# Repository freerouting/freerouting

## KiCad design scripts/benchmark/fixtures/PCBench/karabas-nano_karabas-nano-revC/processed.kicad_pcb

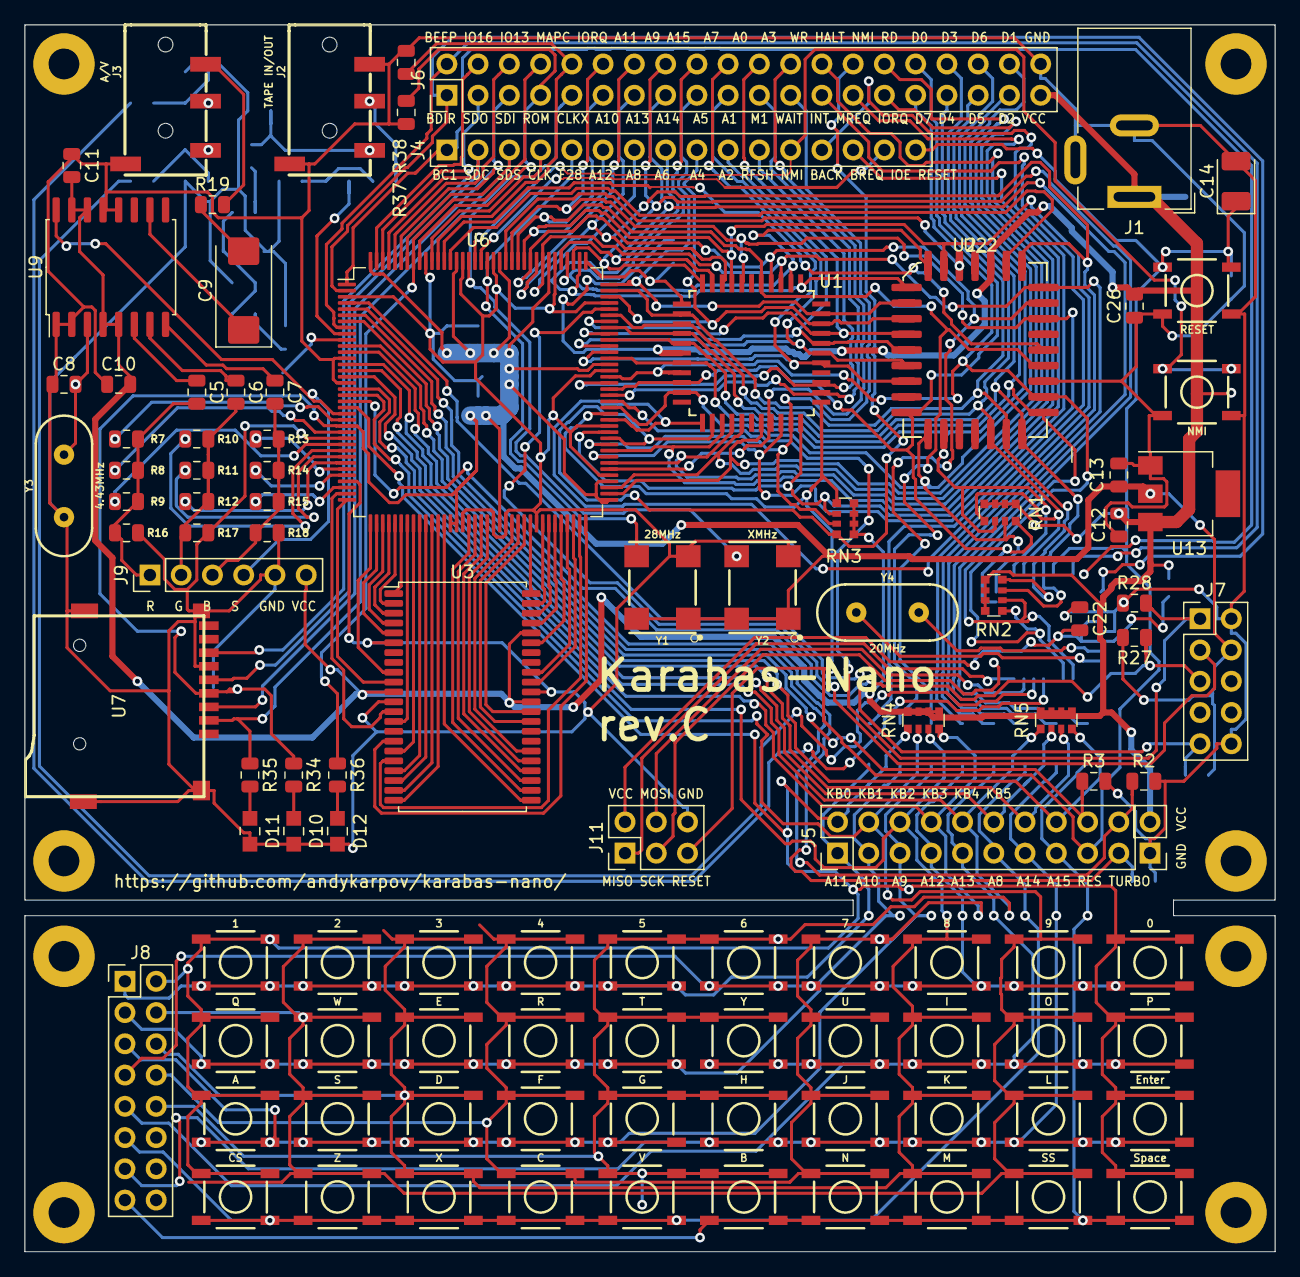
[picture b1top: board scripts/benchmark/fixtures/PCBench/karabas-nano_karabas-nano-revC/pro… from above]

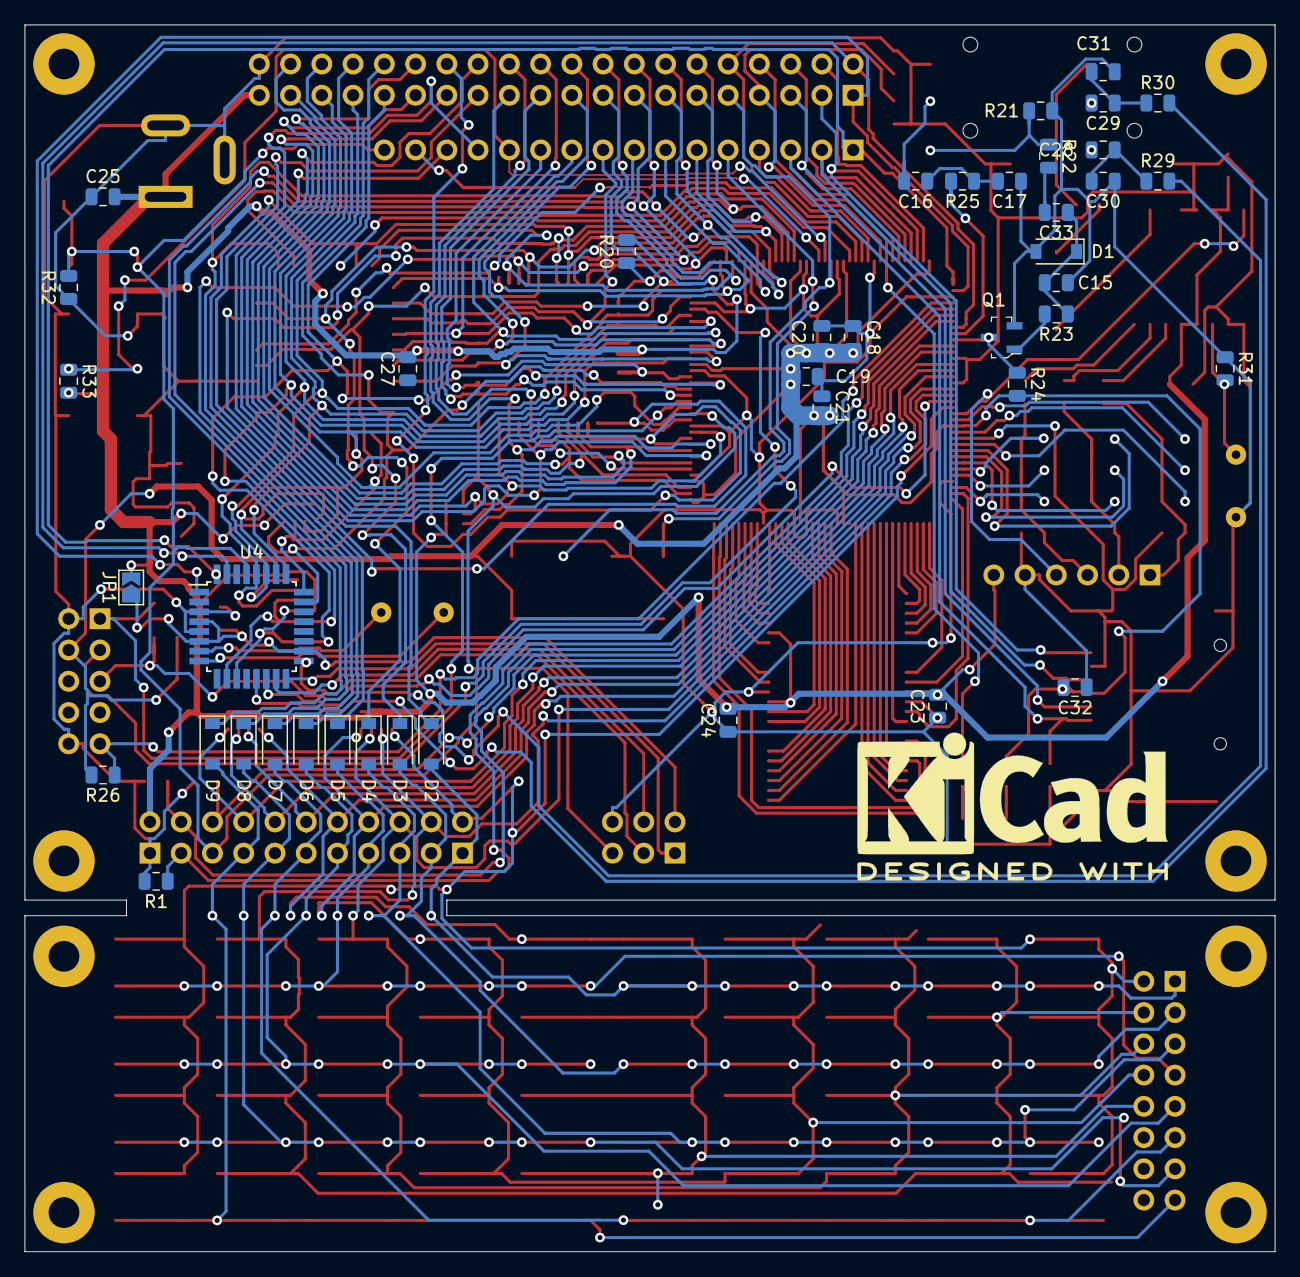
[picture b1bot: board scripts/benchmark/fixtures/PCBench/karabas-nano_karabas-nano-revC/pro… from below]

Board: 2 copper layers, 101.6 x 99.7 mm, 157 parts (42 on the bottom side), 162 nets.

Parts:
C5, C6, C7, C16, C18, C19, C20, C21, C22, C23, C24, C25, C26, C27, C32: 100nF; C_0805_2012Metric
C8: 10p; C_0805_2012Metric
C9: 220uF; CP_EIA-7343-31_Kemet-D_Pad2.25x2.55mm_HandSolder
C10, C11, C12, C13, C28, C29: 10uF; C_0805_2012Metric
C14: 10uF; CP_EIA-3528-21_Kemet-B_Pad1.50x2.35mm_HandSolder
C15, C33: 10nF; C_0805_2012Metric
C17: 3n3; C_0805_2012Metric
C30, C31: 1nF; C_0805_2012Metric
D1, D2, D3, D4, D5, D6, D7, D8, D9: 1N4148W; D_SOD-123
D10: PWR; 0805
D11: SD; 0805
D12: MMC; 0805
H1, H2, H3, H4, H5, H6, H7, H8: MountingHole; MountingHole_2.5mm_Pad
J1: DC 5V; BarrelJack_Wuerth_6941xx301002
J2: TAPE IN/OUT; AUDIO_JACK_3.5MM_SMD
J3: A/V; AUDIO_JACK_3.5MM_SMD
J4: BUS; PinHeader_1x16_P2.54mm_Vertical
J5: KEYBOARD; PinHeader_2x10_P2.54mm_Vertical
J6: BUS; PinHeader_2x20_P2.54mm_Vertical
J7: JTAG; PinHeader_2x05_P2.54mm_Vertical
J8: KEYBOARD; PinHeader_2x08_P2.54mm_Vertical
J9: RGB; PinHeader_1x06_P2.54mm_Vertical
J10: PWR; PinHeader_1x02_P2.54mm_Vertical
J11: AVR ISP; PinHeader_2x03_P2.54mm_Vertical
JP1: SolderJumper_2_Open; SolderJumper-2_P1.3mm_Open_TrianglePad1.0x1.5mm
Q1: BC846B; SOT-23-3
R1, R2, R3, R21, R23, R24, R26, R27, R28, R29, R30, R33, R37, R38: 10k; R_0805_2012Metric
R7, R10, R13, R22: 510; R_0805_2012Metric
R8, R11, R14: 1k; R_0805_2012Metric
R9, R12, R15: 2k; R_0805_2012Metric
R16, R17, R18, R19: 75; R_0805_2012Metric
R20: 2k2; R_0805_2012Metric
R25: 33k; R_0805_2012Metric
R31: 4,7M; R_0805_2012Metric
R32: 47k; R_0805_2012Metric
R34, R35, R36: 470; R_0805_2012Metric
RN1, RN2, RN3, RN4, RN5: 10k; R_Array_Convex_4x0612
SW1: RESET; TACTILE_SWITCH_SMD_5.2MM
SW2: NMI; TACTILE_SWITCH_SMD_5.2MM
SW3: 1; TACTILE_SWITCH_SMD_5.2MM
SW4: 2; TACTILE_SWITCH_SMD_5.2MM
SW5: 3; TACTILE_SWITCH_SMD_5.2MM
SW6: 4; TACTILE_SWITCH_SMD_5.2MM
SW7: 5; TACTILE_SWITCH_SMD_5.2MM
SW8: 6; TACTILE_SWITCH_SMD_5.2MM
SW9: 7; TACTILE_SWITCH_SMD_5.2MM
SW10: 8; TACTILE_SWITCH_SMD_5.2MM
SW11: 9; TACTILE_SWITCH_SMD_5.2MM
SW12: 0; TACTILE_SWITCH_SMD_5.2MM
SW13: Q; TACTILE_SWITCH_SMD_5.2MM
SW14: A; TACTILE_SWITCH_SMD_5.2MM
SW15: CS; TACTILE_SWITCH_SMD_5.2MM
SW16: W; TACTILE_SWITCH_SMD_5.2MM
SW17: S; TACTILE_SWITCH_SMD_5.2MM
SW18: Z; TACTILE_SWITCH_SMD_5.2MM
SW19: E; TACTILE_SWITCH_SMD_5.2MM
SW20: D; TACTILE_SWITCH_SMD_5.2MM
SW21: X; TACTILE_SWITCH_SMD_5.2MM
SW22: R; TACTILE_SWITCH_SMD_5.2MM
SW23: F; TACTILE_SWITCH_SMD_5.2MM
SW24: C; TACTILE_SWITCH_SMD_5.2MM
SW25: T; TACTILE_SWITCH_SMD_5.2MM
SW26: G; TACTILE_SWITCH_SMD_5.2MM
SW27: V; TACTILE_SWITCH_SMD_5.2MM
SW28: Y; TACTILE_SWITCH_SMD_5.2MM
SW29: H; TACTILE_SWITCH_SMD_5.2MM
SW30: B; TACTILE_SWITCH_SMD_5.2MM
SW31: U; TACTILE_SWITCH_SMD_5.2MM
SW32: J; TACTILE_SWITCH_SMD_5.2MM
SW33: N; TACTILE_SWITCH_SMD_5.2MM
SW34: I; TACTILE_SWITCH_SMD_5.2MM
SW35: K; TACTILE_SWITCH_SMD_5.2MM
SW36: M; TACTILE_SWITCH_SMD_5.2MM
SW37: O; TACTILE_SWITCH_SMD_5.2MM
SW38: L; TACTILE_SWITCH_SMD_5.2MM
SW39: SS; TACTILE_SWITCH_SMD_5.2MM
SW40: P; TACTILE_SWITCH_SMD_5.2MM
SW41: Enter; TACTILE_SWITCH_SMD_5.2MM
SW42: Space; TACTILE_SWITCH_SMD_5.2MM
U1: Z80; QFP80P1200X1200X160-44N
U2: 27C512; PLCC-32_11.4x14.0mm_P1.27mm
U2_2: 27C512; PLCC-32_11.4x14.0mm_P1.27mm-bigpads
U3: BS62LV1600; TSOP-II-44_10.16x18.41mm_P0.8mm
U4: ATmega8A-AU; TQFP-32_7x7mm_P0.8mm
U6: EPM3256ATC144; LQFP-144_20x20mm_P0.5mm
U7: MicroSD; GCT-MEM2055-00-190-01-A
U9: AD724; SOIC-16W_7.5x10.3mm_P1.27mm
U13: LM1117-3.3; SOT-223
Y1: 28MHz; OSCILLATOR-SMD-7X5-4PAD
Y2: XMHz; OSCILLATOR-SMD-7X5-4PAD
Y3: 4.43MHz; HC49US
Y4: 20MHz; HC49US

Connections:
+3V3: C13.2, C18.2, C19.2, C20.2, C21.2, C32.2, J7.4, R24.2, R26.2, R27.2, R34.1, U6.24, U6.50, U6.51, U6.58, U6.73, U6.76, U6.95, U6.115, U6.123, U6.130, U6.144, U7.4, U13.2, Y1.1, Y1.4, Y2.1, Y2.4
/A0: J6.20, U1.27, U2.11, U2_2.11, U6.97
/A1: J6.19, U1.28, U2.10, U2_2.10, U6.98
/A2: J4.10, U1.29, U2.9, U2_2.9, U6.100
/A3: J6.22, U1.30, U2.8, U2_2.8, U6.102
/A4: J4.9, U1.31, U2.7, U2_2.7, U6.106
/A5: J6.17, U1.32, U2.6, U2_2.6, U6.108
/A6: J4.8, U1.34, U2.5, U2_2.5, U6.110
/A7: J6.18, U1.35, U2.4, U2_2.4, U6.112
/A8: D7.1, J4.7, U1.36, U2.29, U2_2.29, U6.116
/A9: D4.1, J6.14, U1.37, U2.28, U2_2.28, U6.118
/A10: D3.1, J6.11, U1.38, U2.24, U2_2.24, U6.120
/A11: D2.1, J6.12, U1.40, U2.27, U2_2.27, U6.121
/A12: D5.1, J4.6, U1.41, U2.3, U2_2.3, U6.119
/A13: D6.1, J6.13, U1.42, U2.30, U2_2.30, U6.117
/A14: D8.1, J6.15, U1.43, U6.113
/A15: D9.1, J6.16, U1.44, U6.111
/AVR_MISO: J11.1, U4.16
/AVR_MOSI: J11.4, U4.15
/AVR_SCK: J11.3, U4.17
/AY_BC1: J4.1, U4.32, U6.1
/AY_BDIR: J6.1, U4.1, U6.2
/AY_OUT_L: R30.2, U4.13
/AY_OUT_R: R29.2, U4.14
/B0: R15.1, U6.34
/B1: R14.1, U6.32
/B2: R13.1, U6.31
/BEEPER: J6.2, U4.31, U6.8
/BLUE: C7.2, J9.3, R13.2, R14.2, R15.2, R18.1
/CLK28: J4.5, U6.125, Y1.3
/CLKX: J6.9, U6.128, Y2.3
/CLK_BUS: J4.4, U6.134
/CLK_CPU: R20.1, U1.1, U6.109
/CSYNC: J9.4, U6.22, U9.16
/D0: J6.32, RN1.4, U1.9, U2.13, U2_2.13, U4.23, U6.91
/D1: J6.38, RN1.3, U1.10, U2.14, U2_2.14, U4.24, U6.88
/D2: J6.37, RN1.2, U1.7, U2.15, U2_2.15, U4.25, U6.96
/D3: J6.34, RN1.1, U1.3, U2.18, U2_2.18, U4.26, U6.103
/D4: J6.33, RN2.4, U1.2, U2.19, U2_2.19, U4.27, U6.107
/D5: J6.35, RN2.3, U1.4, U2.20, U2_2.20, U4.28, U6.101
/D6: J6.36, RN2.2, U1.5, U2.21, U2_2.21, U4.10, U6.99
/D7: J6.31, RN2.1, U1.8, U2.22, U2_2.22, U4.11, U6.93
/G0: R12.1, U6.30
/G1: R11.1, U6.29
/G2: R10.1, U6.28
/GREEN: C6.2, J9.2, R10.2, R11.2, R12.2, R17.1
/IO13: J6.6, U6.140
/IO16: J6.4, U6.143
/IOE: J4.15, U6.126
/KA8: D7.2, J5.11, J8.11, SW15.1, SW15.2, SW18.1, SW18.2, SW21.1, SW21.2, SW24.1, SW24.2, SW27.1, SW27.2
/KA9: D4.2, J5.5, J8.5, SW14.1, SW14.2, SW17.1, SW17.2, SW20.1, SW20.2, SW23.1, SW23.2, SW26.1, SW26.2
/KA10: D3.2, J5.3, J8.3, SW13.1, SW13.2, SW16.1, SW16.2, SW19.1, SW19.2, SW22.1, SW22.2, SW25.1, SW25.2
/KA11: D2.2, J5.1, J8.1, SW3.1, SW3.2, SW4.1, SW4.2, SW5.1, SW5.2, SW6.1, SW6.2, SW7.1, SW7.2
/KA12: D5.2, J5.7, J8.7, SW8.1, SW8.2, SW9.1, SW9.2, SW10.1, SW10.2, SW11.1, SW11.2, SW12.1, SW12.2
/KA13: D6.2, J5.9, J8.9, SW28.1, SW28.2, SW31.1, SW31.2, SW34.1, SW34.2, SW37.1, SW37.2, SW40.1, SW40.2
/KA14: D8.2, J5.13, J8.13, SW29.1, SW29.2, SW32.1, SW32.2, SW35.1, SW35.2, SW38.1, SW38.2, SW41.1, SW41.2
/KA15: D9.2, J5.15, J8.15, SW30.1, SW30.2, SW33.1, SW33.2, SW36.1, SW36.2, SW39.1, SW39.2, SW42.1, SW42.2
/KB0: J5.2, J8.2, RN4.1, SW3.3, SW3.4, SW12.3, SW12.4, SW13.3, SW13.4, SW14.3, SW14.4, SW15.3, SW15.4, SW40.3, SW40.4, SW41.3, SW41.4, SW42.3, SW42.4, U6.21
/KB1: J5.4, J8.4, RN4.2, SW4.3, SW4.4, SW11.3, SW11.4, SW16.3, SW16.4, SW17.3, SW17.4, SW18.3, SW18.4, SW37.3, SW37.4, SW38.3, SW38.4, SW39.3, SW39.4, U6.19
/KB2: J5.6, J8.6, RN4.3, SW5.3, SW5.4, SW10.3, SW10.4, SW19.3, SW19.4, SW20.3, SW20.4, SW21.3, SW21.4, SW34.3, SW34.4, SW35.3, SW35.4, SW36.3, SW36.4, U6.18
/KB3: J5.8, J8.8, RN4.4, SW6.3, SW6.4, SW9.3, SW9.4, SW22.3, SW22.4, SW23.3, SW23.4, SW24.3, SW24.4, SW31.3, SW31.4, SW32.3, SW32.4, SW33.3, SW33.4, U6.16
/KB4: J5.10, J8.10, RN5.1, SW7.3, SW7.4, SW8.3, SW8.4, SW25.3, SW25.4, SW26.3, SW26.4, SW27.3, SW27.4, SW28.3, SW28.4, SW29.3, SW29.4, SW30.3, SW30.4, U6.15
/KB5: J5.12, RN5.2, U6.14
/KB6: J5.14, RN5.3, U6.12
/KB7: J5.16, RN5.4, U6.11
/MA0: U3.5, U6.38
/MA1: U3.4, U6.39
/MA2: U3.3, U6.40
/MA3: U3.2, U6.41
/MA4: U3.1, U6.42
/MA5: U3.44, U6.63
/MA6: U3.43, U6.65
/MA7: U3.42, U6.66
/MA8: U3.39, U6.68
/MA9: U3.28, U6.60
/MA10: U3.27, U6.56
/MA11: U3.26, U6.55
/MA12: U3.25, U6.54
/MA13: U3.24, U6.53
/MA14: U3.23, U6.49
/MA15: U3.22, U6.48
/MA16: U3.21, U6.47
/MA17: U3.20, U6.46
/MA18: U3.19, U6.45
/MA19: U3.18, U6.71
/MA20: U3.16, U6.72
/MAGIC: J5.20, R2.1, U6.6
/MAPCOND: J6.8, R36.1, U6.137
/MD0: U3.9, U6.37
/MD1: U3.10, U6.36
/MD2: U3.13, U6.35
/MD3: U3.14, U6.43
/MD4: U3.31, U6.61
/MD5: U3.32, U6.62
/MD6: U3.35, U6.70
/MD7: U3.36, U6.69
/R0: R9.1, U6.27
/R1: R8.1, U6.25
/R2: R7.1, U6.23
/RED: C5.2, J9.1, R7.2, R8.2, R9.2, R16.1
/ROM_A14: U2.31, U2_2.31, U6.131
/ROM_A15: U2.2, U2_2.2, U6.122
/SD_CLK: J4.2, U6.141, U7.5
/SD_DI: J6.5, U6.139, U7.3
/SD_DO: J6.3, U6.142, U7.7
/SPECIAL: J5.18, R3.1, U6.7
/TCK: J7.1, R28.2, U6.89
/TDI: J7.9, R26.1, U6.4
/TDO: J7.3, U6.104
/TMS: J7.5, R27.1, U6.20
/TURBO: J5.19, R1.1, U6.5
/VCCJP: C22.2, J11.2, JP1.1, U4.4, U4.6, U4.18
/~BTN_NMI: J4.12, R33.1, SW2.1, SW2.2, U6.127
/~BUSACK: J4.13, U1.20, U6.80
/~BUSREQ: J4.14, RN3.2, U1.22, U6.84
/~BUS_IORQGE: J6.10, R38.1, U6.133
/~BUS_ROMCS: J6.7, R37.1, U6.136
/~HALT: J6.26, U1.14, U6.81
/~INT: J6.25, U1.12, U6.86
/~IORQ: J6.29, U1.16, U6.75
/~M1: J6.21, U1.24, U6.90
/~MRD: U3.41, U6.67
/~MREQ: J6.27, U1.15, U6.79
/~MWR: U3.17, U6.44
/~NMI: J6.28, RN3.4, U1.13, U6.83
/~RD: J6.30, U1.18, U6.74
/~RFSH: J4.11, U1.25, U6.92
/~ROMCS: U2.25, U2_2.25, U6.132
/~SD_CS: J4.3, R35.1, U6.138, U7.2
/~WAIT: J6.23, RN3.3, U1.21, U6.82
/~WR: J6.24, U1.19, U6.78
GND: C8.1, C10.1, C11.1, C12.1, C13.1, C14.2, C15.1, C17.1, C18.1, C19.1, C20.1, C21.1, C22.1, C23.1, C24.1, C25.1, C26.1, C30.1, C31.1, C32.1, D1.2, D10.2, D11.2, D12.2, J1.2, J1.3, J2.1, J2.2, J3.1, J6.40, J7.2, J7.10, J9.5, J10.1, J11.6, Q1.2, R1.2, R2.2, R3.2, R16.2, R17.2, R18.2, R21.1, R28.1, R31.1, R32.1, R37.2, R38.2, SW1.3, SW1.4, SW2.3, SW2.4, U2.23, U2_2.23, U3.6, U3.12, U3.34, U4.3, U4.5, U6.3, U6.13, U6.17, U6.26, U6.33, U6.52, U6.57, U6.59, U6.64, U6.77, U6.85, U6.94, U6.105, U6.114, U6.124, U6.129, U6.135, U7.6, U7.10, U7.~, U9.1, U9.2, U9.12, U9.13, U13.1, Y1.2, Y2.2, Y3.1
unnamed: C5.1, U9.6
unnamed: C6.1, U9.7
unnamed: C7.1, U9.8
unnamed: C8.2, R31.2, U9.3, Y3.2
unnamed: C9.1, U9.10
unnamed: C9.2, R19.1
unnamed: C15.2, C33.1, D1.1, R23.1
unnamed: C16.1, C17.2, R25.1
unnamed: C16.2, J2.3
unnamed: C28.1, C30.2, R29.1
unnamed: C28.2, J3.4
unnamed: C29.1, C31.2, R30.1
unnamed: C29.2, J3.3
unnamed: C33.2, R22.2
unnamed: D10.1, R34.2
unnamed: D11.1, R35.2
unnamed: D12.1, R36.2
unnamed: J2.4, R21.2, R22.1
unnamed: J3.2, R19.2
unnamed: Q1.1, R23.2
unnamed: U2.1, U2_2.1
unnamed: U2.12, U2_2.12
unnamed: U2.17, U2_2.17
unnamed: U2.26, U2_2.26
unnamed: U4.7, Y4.2
unnamed: U4.8, Y4.1
TAPE_IN: Q1.3, R24.1, U6.10
TAPE_OUT: R25.2, U6.9
VCC: C10.2, C11.2, C12.2, C23.2, C24.2, C25.2, C26.2, C27.2, J1.1, J6.39, J9.6, J10.2, JP1.2, R20.2, R33.2, RN1.5, RN1.6, RN1.7, RN1.8, RN2.5, RN2.6, RN2.7, RN2.8, RN3.5, RN3.6, RN3.7, RN3.8, RN4.5, RN4.6, RN4.7, RN4.8, RN5.5, RN5.6, RN5.7, RN5.8, U1.6, U2.32, U2_2.32, U3.11, U3.33, U3.40, U9.4, U9.5, U9.14, U9.15, U13.3
~RESET: C14.1, J4.16, J5.17, J11.5, R32.2, RN3.1, SW1.1, SW1.2, U1.23, U4.29, U6.87

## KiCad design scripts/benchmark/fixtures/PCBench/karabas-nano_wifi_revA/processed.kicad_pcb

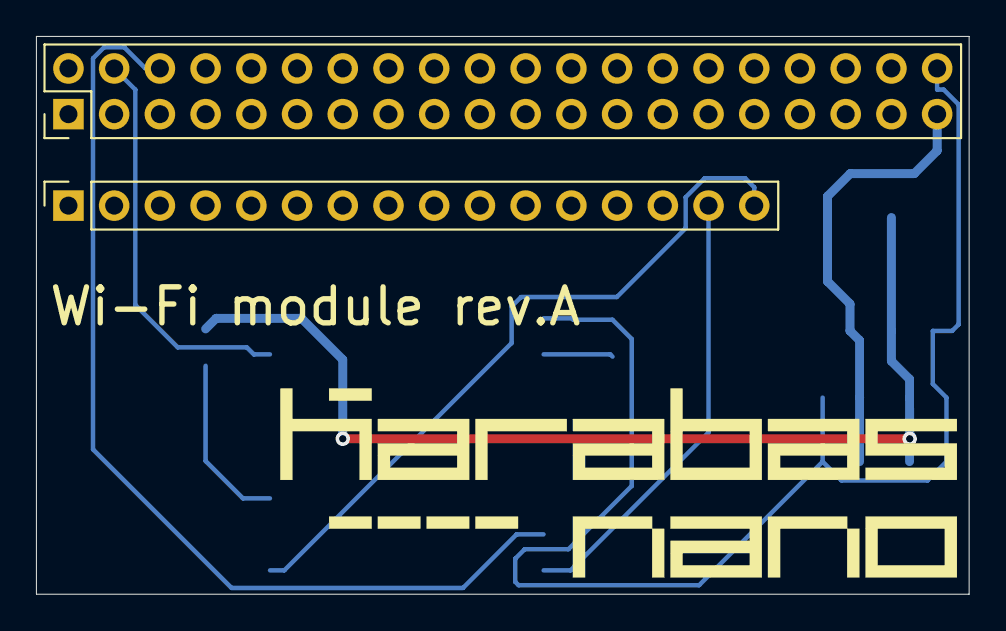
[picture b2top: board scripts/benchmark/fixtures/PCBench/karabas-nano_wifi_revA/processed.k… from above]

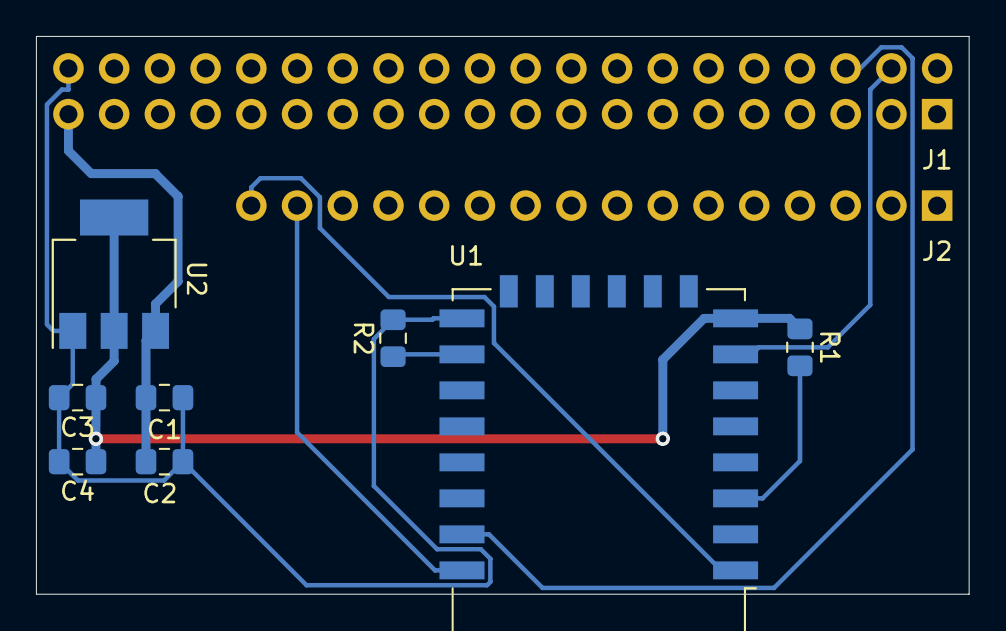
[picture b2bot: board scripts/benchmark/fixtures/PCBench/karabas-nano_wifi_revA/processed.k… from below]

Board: 2 copper layers, 51.8 x 31.0 mm, 10 parts (8 on the bottom side), 9 nets.

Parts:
C1, C4: 100nF; C_0805_2012Metric_Pad1.15x1.40mm_HandSolder
C2, C3: 1uF; C_0805_2012Metric_Pad1.15x1.40mm_HandSolder
J1: ZX BUS; PinHeader_2x20_P2.54mm_Vertical
J2: ZX BUS; PinSocket_1x16_P2.54mm_Vertical
R1, R2: 10k; R_0805_2012Metric_Pad1.15x1.40mm_HandSolder
U1: ESP-12E
U2: AMS1117-3.3; SOT-223-3_TabPin2

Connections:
+3V3: C3.1, C4.1, R1.1, U1.8, U2.2
GND: C1.2, C2.2, C3.2, C4.2, J1.40, R2.2, U1.15, U2.1
unnamed: R1.2, U1.3
unnamed: R2.1, U1.16
UART_CTS: J1.4, U1.7
UART_RX: J2.15, U1.22
UART_TX: J1.6, U1.21
VCC: C1.1, C2.1, J1.39, U2.3
~RESET: J2.16, U1.1
